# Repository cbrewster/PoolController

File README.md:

Pool Controller
---

Embedded Systems Design

A system to control your pool controller.

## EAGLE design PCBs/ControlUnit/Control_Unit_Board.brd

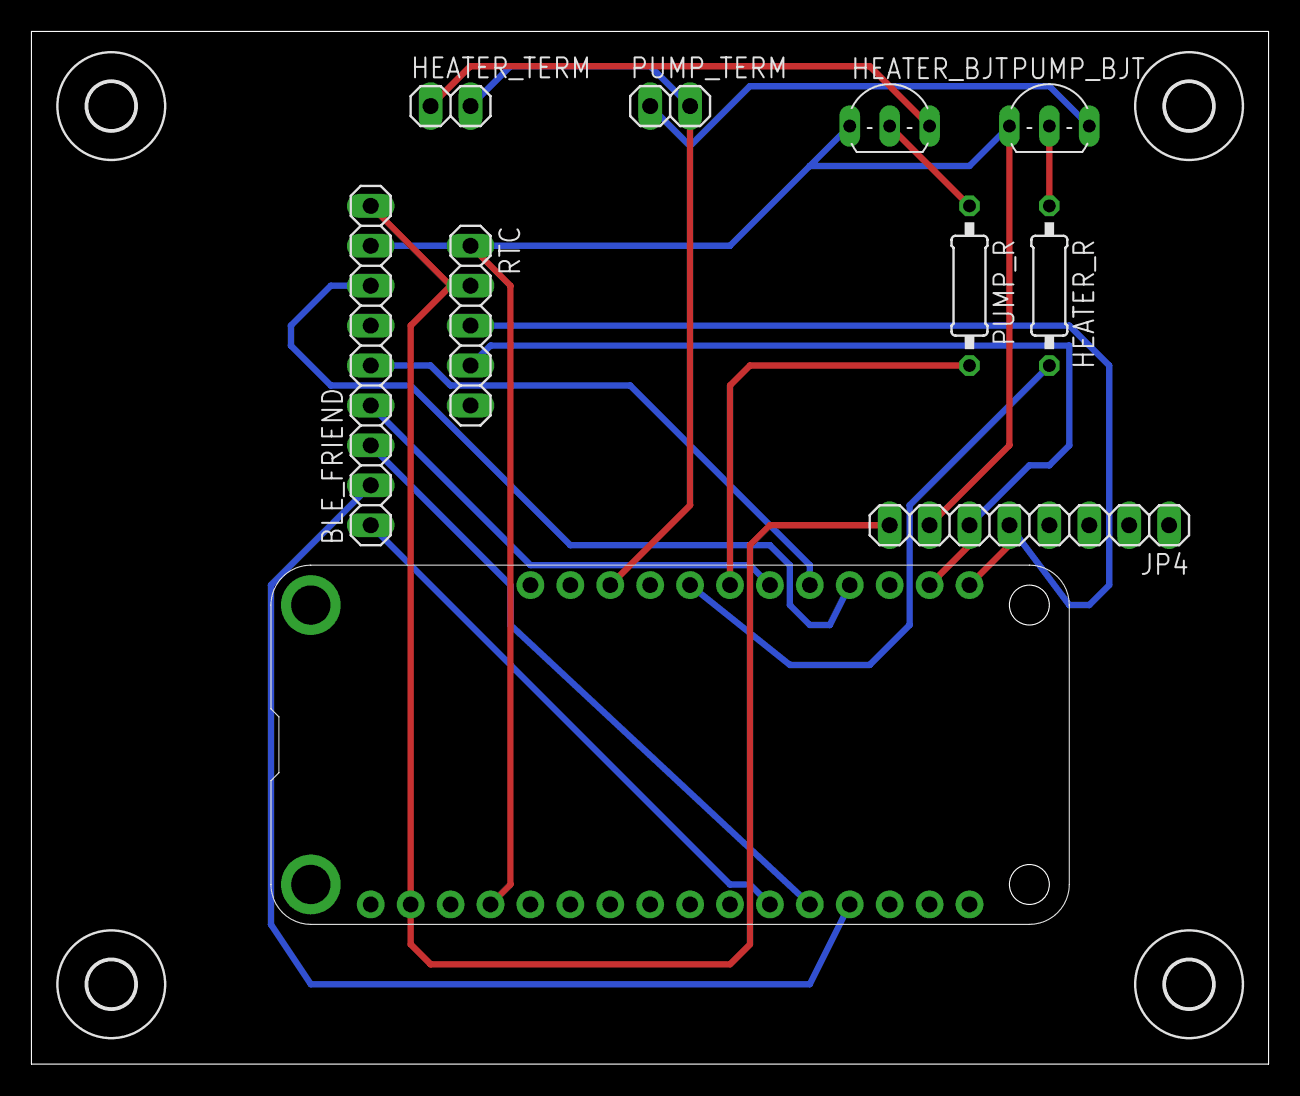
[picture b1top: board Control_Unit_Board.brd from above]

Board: 2 copper layers, 78.7 x 65.7 mm, 14 parts (0 on the bottom side), 17 nets.

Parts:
BLE_FRIEND: 1X09
HEATER_BJT: 2N2222; TO92-EBC-OVAL
HEATER_R: 0207/10
HEATER_TERM: 1X02
JP4: 1X08
MS1: FEATHERWING_NODIM; FEATHERWING_DIM
PUMP_BJT: 2N2222; TO92-EBC-OVAL
PUMP_R: 0207/10
PUMP_TERM: 1X02
RTC: 1X05
U$1, U$2, U$3, U$4: 3,0

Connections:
GND: BLE_FRIEND.8, HEATER_BJT.E, JP4.7, MS1.4, PUMP_BJT.E, RTC.1
unnamed: BLE_FRIEND.2, MS1.13
unnamed: BLE_FRIEND.3, MS1.12
unnamed: BLE_FRIEND.1, MS1.11
unnamed: BLE_FRIEND.5, MS1.21
unnamed: MS1.23, PUMP_R.2
unnamed: HEATER_R.2, MS1.24
unnamed: HEATER_R.1, PUMP_BJT.B
unnamed: HEATER_BJT.B, PUMP_R.1
unnamed: JP4.5, MS1.17, RTC.3
unnamed: PUMP_BJT.C, PUMP_TERM.1
unnamed: HEATER_BJT.C, HEATER_TERM.1
unnamed: JP4.6, MS1.18, RTC.4
unnamed: BLE_FRIEND.7, MS1.20
S$1: BLE_FRIEND.4, MS1.22
USB: HEATER_TERM.2, MS1.26, PUMP_TERM.2
VCC: BLE_FRIEND.9, JP4.8, MS1.2, RTC.2

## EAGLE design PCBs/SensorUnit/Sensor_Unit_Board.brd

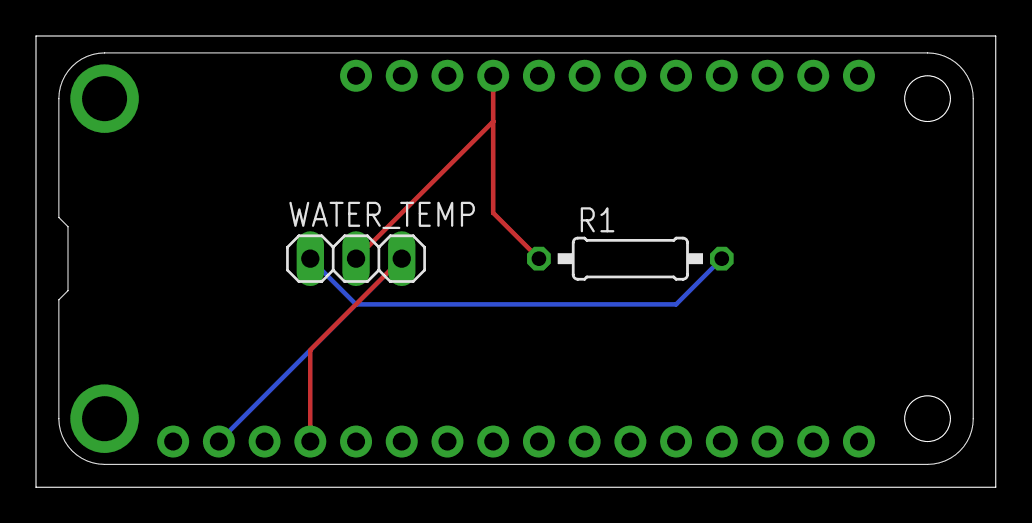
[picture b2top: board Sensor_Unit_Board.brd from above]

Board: 2 copper layers, 53.3 x 25.1 mm, 3 parts (0 on the bottom side), 3 nets.

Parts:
MS1: FEATHERWING_NODIM; FEATHERWING_DIM
R1: 0207/10
WATER_TEMP: 1X03

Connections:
GND: MS1.4, WATER_TEMP.3
unnamed: MS1.25, R1.1, WATER_TEMP.2
VCC: MS1.2, R1.2, WATER_TEMP.1

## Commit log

2019-02-06 Get temperature sensor values
2019-02-07 Transmit pool temperature and depth
2019-02-07 Fix bug where only depth was sent
    Add comments
2019-02-07 Add Receive Sensor Data
2019-02-07 Add relay testing script
2019-02-11 Build basic mobile app interface
2019-02-11 Move indicator to right of title
2019-02-14 Implement thermostat and pump schedule
2019-02-21 Add flutter blue
2019-02-21 Add control center program
2019-02-22 Advertise BLE Service
2019-02-25 Add initial PCB files
2019-02-28 Current Connected Fritzing Files
    Sensor unit is done but needs to be checked. The control unit has a few issues that need to be worked out.
2019-02-28 Implement thermostat bluetooth temp
2019-02-28 Implement air temperature sensor
2019-02-28 Cleanup characteristic reading
2019-03-03 Correct connections for PCB designs
2019-03-03 Old PCBs deleted, new ones updated
2019-03-04 Add heater on characteristic
2019-03-04 Show loading screen until characteristics are loaded
2019-03-04 Use callbacks
2019-03-06 Adding eagle pcbs
2019-03-07 Control Unit PCB finished, Sensor unit almost
2019-03-07 Both Gerbers Finished
2019-03-07 Revert "Both Gerbers Finished"
    This reverts commit 50d65f6ba1f1fa0185709d21e464bfc3a5d3b340.
2019-03-07 Correct Gerbers
2019-03-11 Fix buffer overflow bug Fix thermostat Get thermostat working
2019-03-11 Cleanup and restructure
2019-03-11 Cleanup bluetooth communication
2019-03-11 Update names and comments
    Dispose control unit on disconnect
2019-03-14 Use phone time to adjust RTC time
2019-03-14 Cleanup update logic
    Make timestamp label look nicer
2019-03-28 Add pump schedule characteristics
2019-04-03 Finish pool scheduling
2019-04-10 Updated CU Gerber
    Updated control unit gerber files and FreeDFM results for both units
2019-04-17 Increase max heater temp to 104
2019-04-23 Update default state to off
